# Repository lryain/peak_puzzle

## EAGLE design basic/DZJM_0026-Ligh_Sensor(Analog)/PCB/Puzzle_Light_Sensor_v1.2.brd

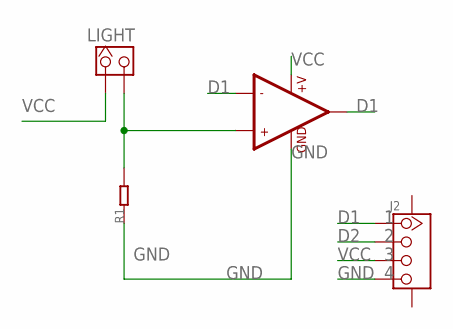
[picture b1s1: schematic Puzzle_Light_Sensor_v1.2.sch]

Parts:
J2: TWIG-4P-2.0-SMD-FEMALE-REINFORCE'DD'; 4P-SMD-2.0
LIGHT: HEADER_1X2_2.54; CK_1*2
R1: R0603; 0603
U1: LMV358; SO08

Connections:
D1: J2.1, U1.1 (OUT1), U1.2 (-IN1)
D2: J2.2
GND: J2.4, R1.1, U1.4 (GND)
unnamed: LIGHT.2, R1.2, U1.3 (+IN1)
VCC: J2.3, LIGHT.1, U1.8 (+V)

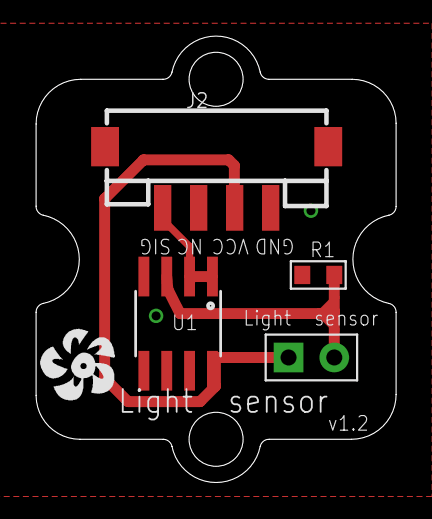
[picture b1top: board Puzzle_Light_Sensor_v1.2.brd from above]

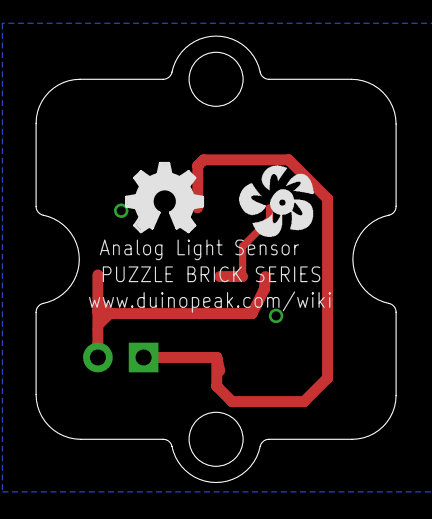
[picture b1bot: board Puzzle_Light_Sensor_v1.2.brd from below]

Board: 2 copper layers, 20.0 x 24.8 mm, 8 parts (2 on the bottom side), 4 nets.

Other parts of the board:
U$2: OPHW-LOGO-FILL-150
U$3: DZJM-B20-1P
U$4, U$6: DUINOFUN-LOGO-PCB-0.55

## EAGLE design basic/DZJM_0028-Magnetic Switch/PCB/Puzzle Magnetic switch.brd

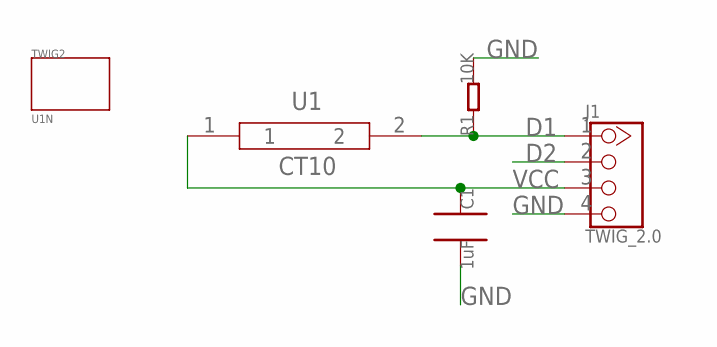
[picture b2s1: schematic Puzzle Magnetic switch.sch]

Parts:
C1: 1uF; 0805
J1: TWIG_2.0; 2.0_1X4
R1: 10K; 0805
TWIG2: U1N
U1: MAGNETISM

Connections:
D1: J1.1, R1.1, U1.2
D2: J1.2
GND: C1.2, J1.4, R1.2
VCC: C1.1, J1.3, U1.1

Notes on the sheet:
CT10

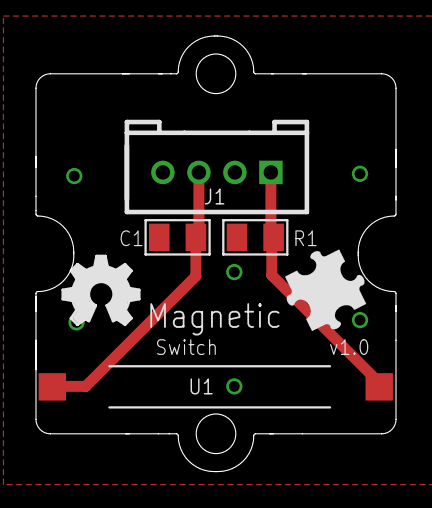
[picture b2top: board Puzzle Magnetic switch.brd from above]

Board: 2 copper layers, 20.0 x 24.2 mm, 7 parts (0 on the bottom side), 3 nets.

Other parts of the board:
U$1: BRICK-LOGO-MIL-0.5
U$2: OPHW-LOGO-FILL-150

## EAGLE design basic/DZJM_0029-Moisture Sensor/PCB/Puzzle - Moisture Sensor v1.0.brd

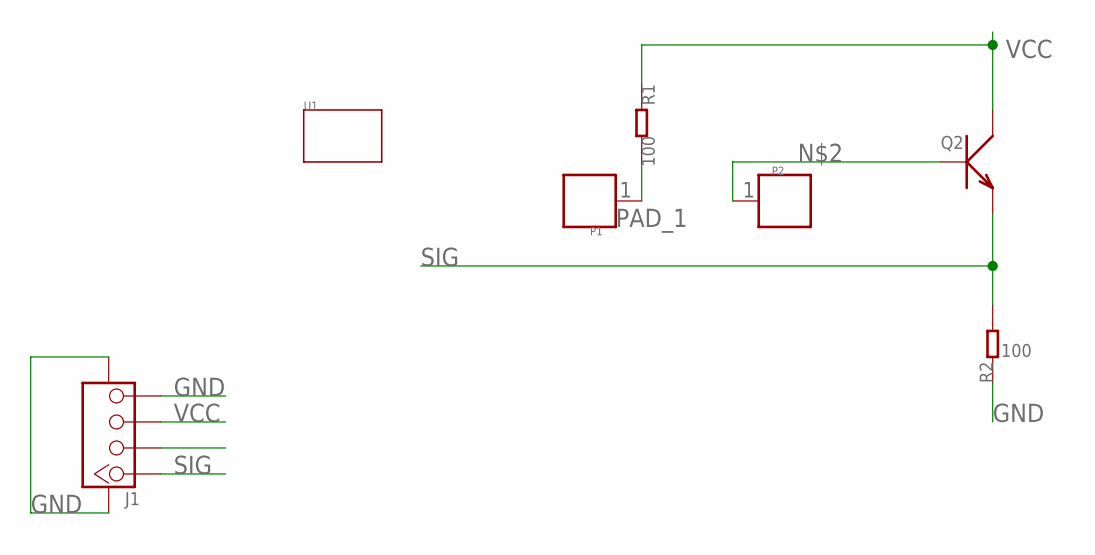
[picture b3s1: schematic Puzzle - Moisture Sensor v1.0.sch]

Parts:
J1: TWIG-4P-2.0-SMD-FEMALE-REINFORCE'90D'; 4P-SMD-2.0-90D
P1, P2: PAD.03; 1P-SMD-0.76X0.76
Q2: TRANSISTOR-NPN-SOT23''; SOT23
R1, R2: 100; 0603
U1: TWIG'SPECIAL'; 3U-DIM-W/-DRILL-SPECIAL

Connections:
GND: J1.4, J1.SS1, J1.SS2, R2.1
unnamed: P2.1, Q2.1 (B)
PAD_1: P1.1, R1.2
SIG: J1.1, Q2.2 (E), R2.2
VCC: J1.3, Q2.3 (C), R1.1

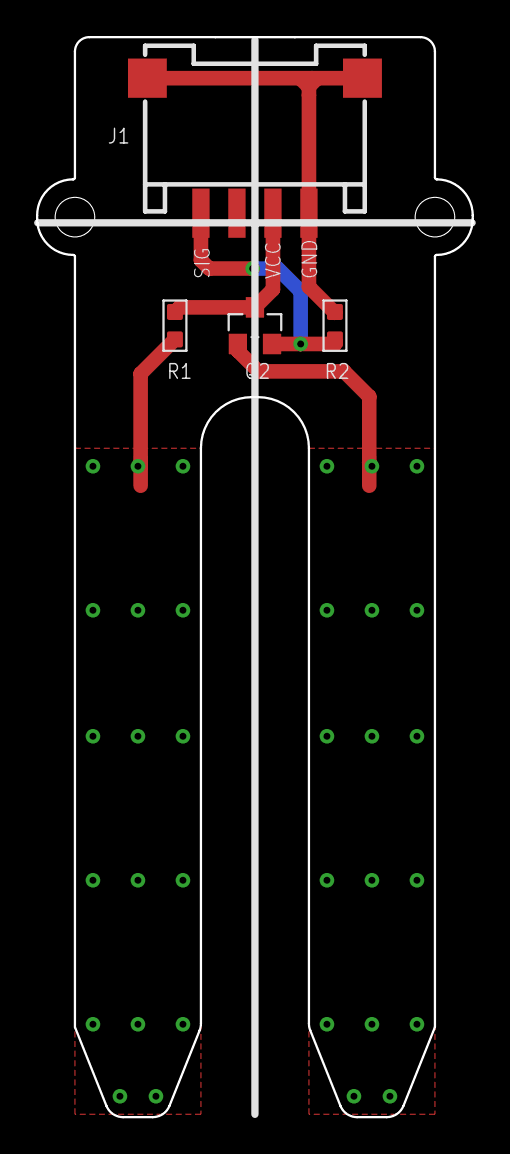
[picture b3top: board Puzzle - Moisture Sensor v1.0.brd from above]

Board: 2 copper layers, 24.2 x 60.0 mm, 9 parts (1 on the bottom side), 5 nets.

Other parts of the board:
U$2: OSHW_FILLX200_NOTEXT
U$3: BRICK-LOGO-2-B-MIL-0.6

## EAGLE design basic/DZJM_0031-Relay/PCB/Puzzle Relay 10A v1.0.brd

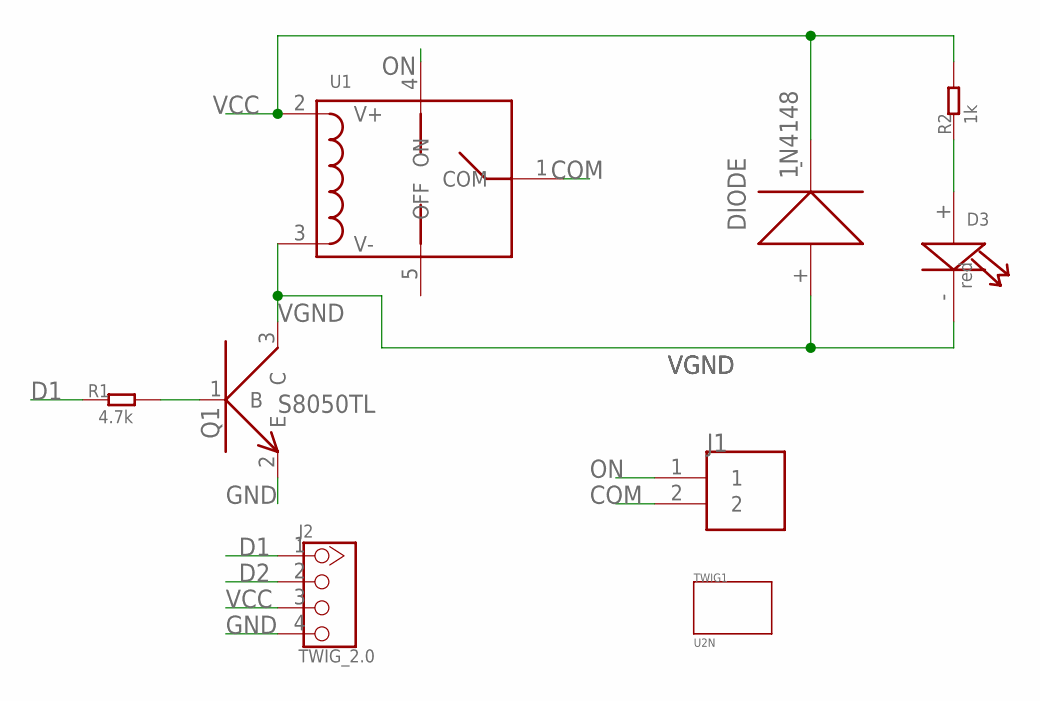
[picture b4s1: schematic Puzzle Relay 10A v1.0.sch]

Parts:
D3: red; LED0805
DIODE: 1N4148; DIODE1206
J1: CON2
J2: TWIG_2.0; 2.0_1X4
Q1: NPN_9013; SOT23
R1: 4.7k; 0603
R2: 1k; 0603
TWIG1: U2N
U1: RELAY

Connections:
COM: J1.2, U1.1 (COM)
D1: J2.1, R1.1
D2: J2.2
GND: J2.4, Q1.2 (E)
unnamed: D3.+, R2.1
unnamed: Q1.1 (B), R1.2
ON: J1.1, U1.4 (ON)
VCC: DIODE.-, J2.3, R2.2, U1.2 (V+)
VGND: D3.-, DIODE.+, Q1.3 (C), U1.3 (V-)

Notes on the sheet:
S8050TL

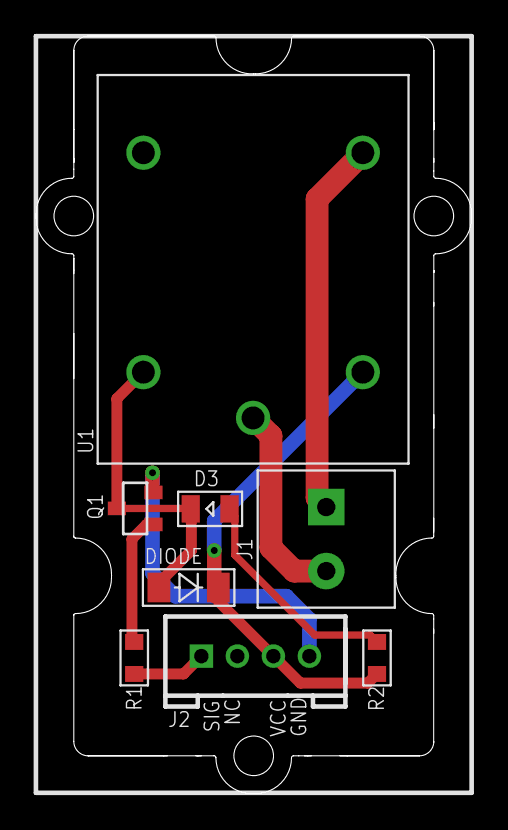
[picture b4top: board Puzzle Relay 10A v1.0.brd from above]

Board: 2 copper layers, 24.2 x 42.1 mm, 11 parts (1 on the bottom side), 8 nets.

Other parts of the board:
U$2: OSHW_FILLX200_NOTEXT
U$3: BRICK-LOGO-2-B-MIL-0.6

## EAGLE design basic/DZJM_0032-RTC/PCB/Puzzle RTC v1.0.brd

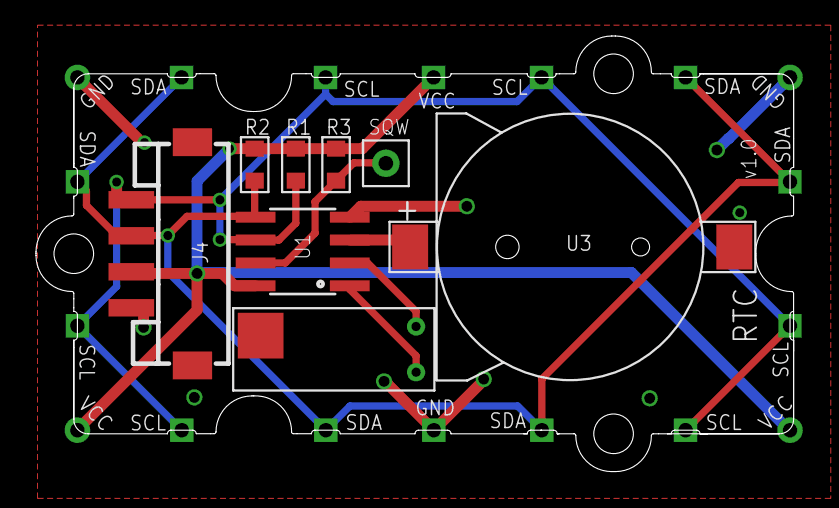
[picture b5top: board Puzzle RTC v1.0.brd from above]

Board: 2 copper layers, 42.1 x 24.2 mm, 9 parts (0 on the bottom side), 8 nets.

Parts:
J4: TWIG_2.0DD'DD'; 2.0_1X4DD
R1, R2, R3: 4.7k; 0603
SQW: CK_1X132; CK_1X1
TWIG1: TWIG-U2; U2
U1: DS1307; SO08
U3: BATTERY1225_SMT
X1: 32.768k; XTL_S

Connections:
GND: J4.4, J4.SS1, J4.SS2, TWIG1.10, TWIG1.15, TWIG1.16, U1.4, U3.1
S/O: R3.1, SQW.P$1, U1.7
SCL: J4.1, R1.1, TWIG1.2, TWIG1.4, TWIG1.7, TWIG1.8, TWIG1.12, TWIG1.13, U1.6
SDA: J4.2, R2.1, TWIG1.1, TWIG1.5, TWIG1.6, TWIG1.9, TWIG1.11, TWIG1.14, U1.5
VBAT: U1.3, U3.2
VCC: J4.3, R1.2, R2.2, R3.2, TWIG1.3, TWIG1.17, TWIG1.18, U1.8
X1: U1.1, X1.1
X2: U1.2, X1.2

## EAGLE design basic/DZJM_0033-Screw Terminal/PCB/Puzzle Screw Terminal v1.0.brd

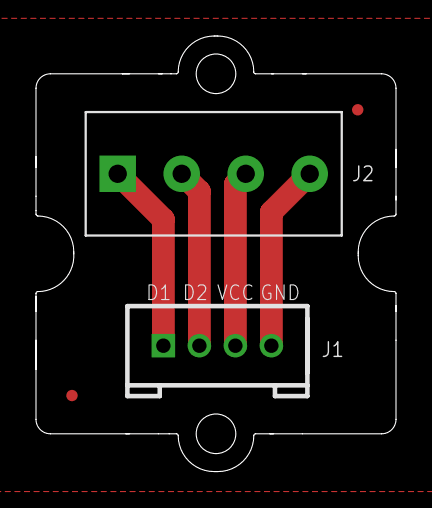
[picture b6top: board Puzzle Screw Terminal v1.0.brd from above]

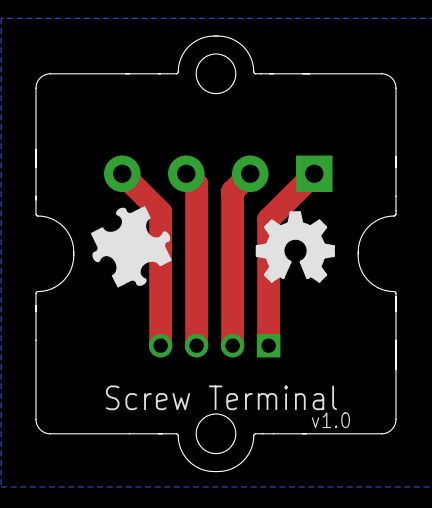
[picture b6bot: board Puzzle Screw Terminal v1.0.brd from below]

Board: 2 copper layers, 20.0 x 24.2 mm, 7 parts (2 on the bottom side), 4 nets.

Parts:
E$1: BRICK-LOGO-MIL-0.5
J1: TWIG; 4P-LEADED-2.0
J2: 4P-3.5
LOGO1: LOGO-OSHW-FILLX0150-NT; OSHW_FILLX150_NOTEXT
MARK1, MARK2: ROUND-MARK-0.635
TWIG2: U1N; 1U-DIM-W/-DRILL

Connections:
D1: J1.1, J2.1
D2: J1.2, J2.2
GND: J1.4, J2.4
VCC: J1.3, J2.3

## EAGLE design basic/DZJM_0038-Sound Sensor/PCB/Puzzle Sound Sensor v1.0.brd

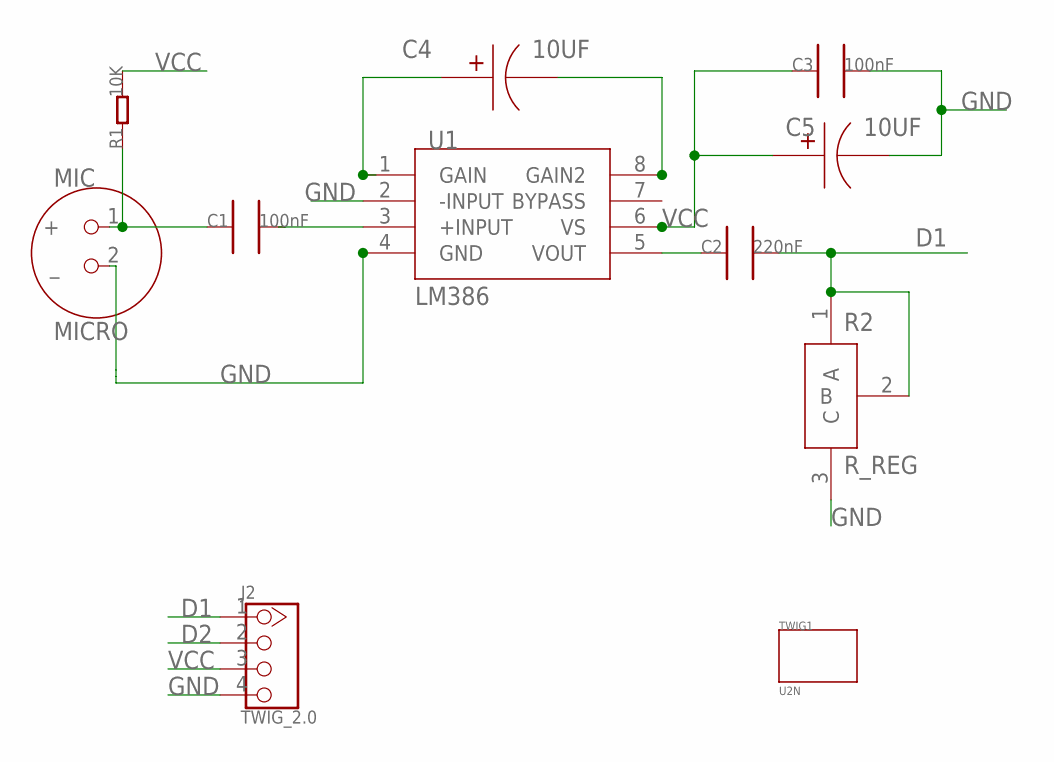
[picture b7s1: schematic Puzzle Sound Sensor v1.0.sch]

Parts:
C1, C3: 100nF; 0603
C2: 220nF; 0603
C4, C5: 10UF; C_TAN1206
J2: TWIG_2.0; 2.0_1X4
MIC: MICRO
R1: 10K; 0603
R2: R_REG
TWIG1: U2N
U1: LM386; SO08

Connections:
D1: C2.2, J2.1, R2.1 (A), R2.2 (B)
D2: J2.2
GND: C3.2, C5.2, J2.4, MIC.2 (_), R2.3 (C), U1.2 (-INPUT), U1.4 (GND)
unnamed: C4.2, U1.8 (GAIN2)
unnamed: C1.1, MIC.1 (+), R1.1
unnamed: C1.2, U1.3 (+INPUT)
unnamed: C4.1, U1.1 (GAIN)
unnamed: C2.1, U1.5 (VOUT)
VCC: C3.1, C5.1, J2.3, R1.2, U1.6 (VS)

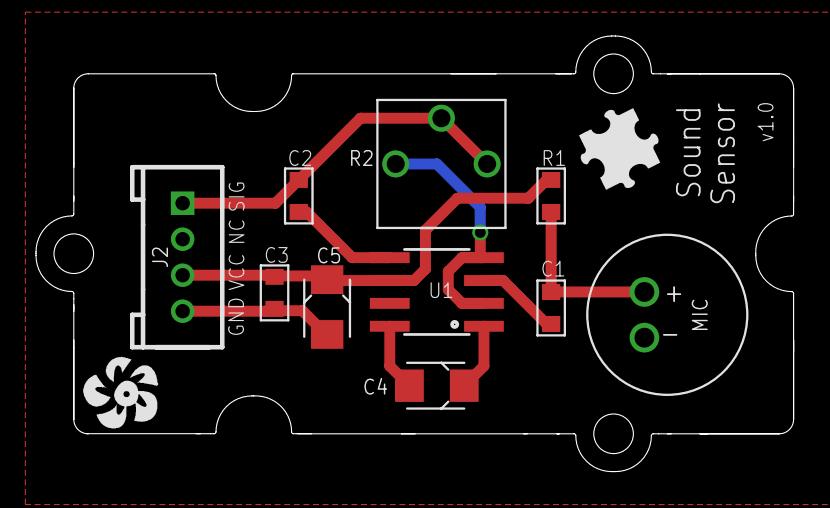
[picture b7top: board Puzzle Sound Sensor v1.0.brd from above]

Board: 2 copper layers, 42.1 x 24.2 mm, 13 parts (0 on the bottom side), 8 nets.

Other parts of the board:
U$1: BRICK-LOGO-MIL-0.5
U$2: DUINOFUN-LOGO-PCB-0.55

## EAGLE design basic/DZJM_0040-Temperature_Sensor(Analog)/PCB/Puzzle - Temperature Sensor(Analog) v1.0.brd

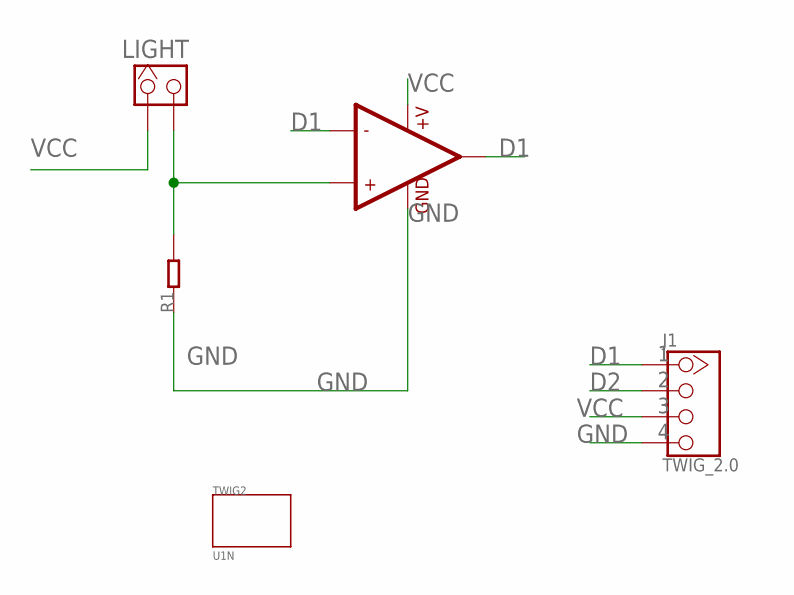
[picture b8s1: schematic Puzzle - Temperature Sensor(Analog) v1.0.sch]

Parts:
J1: TWIG_2.0; 2.0_1X4
LIGHT: HEADER_1X2_2.54; CK_1*2
R1: R0603; 0603
TWIG2: U1N
U1: LMV358; SO08

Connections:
D1: J1.1, U1.1 (OUT1), U1.2 (-IN1)
D2: J1.2
GND: J1.4, R1.1, U1.4 (GND)
unnamed: LIGHT.2, R1.2, U1.3 (+IN1)
VCC: J1.3, LIGHT.1, U1.8 (+V)

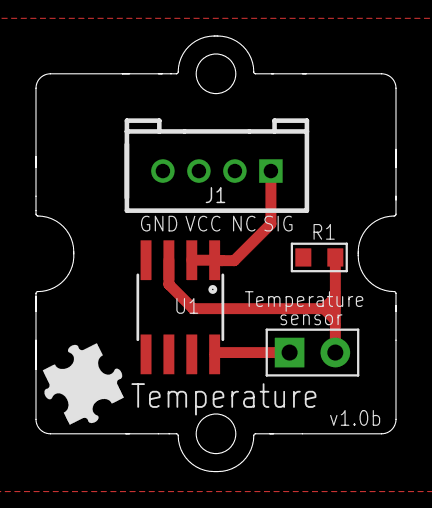
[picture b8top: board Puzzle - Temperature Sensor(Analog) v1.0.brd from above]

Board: 2 copper layers, 20.0 x 24.2 mm, 6 parts (0 on the bottom side), 4 nets.

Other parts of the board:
U$2: BRICK-LOGO-MIL-0.5
